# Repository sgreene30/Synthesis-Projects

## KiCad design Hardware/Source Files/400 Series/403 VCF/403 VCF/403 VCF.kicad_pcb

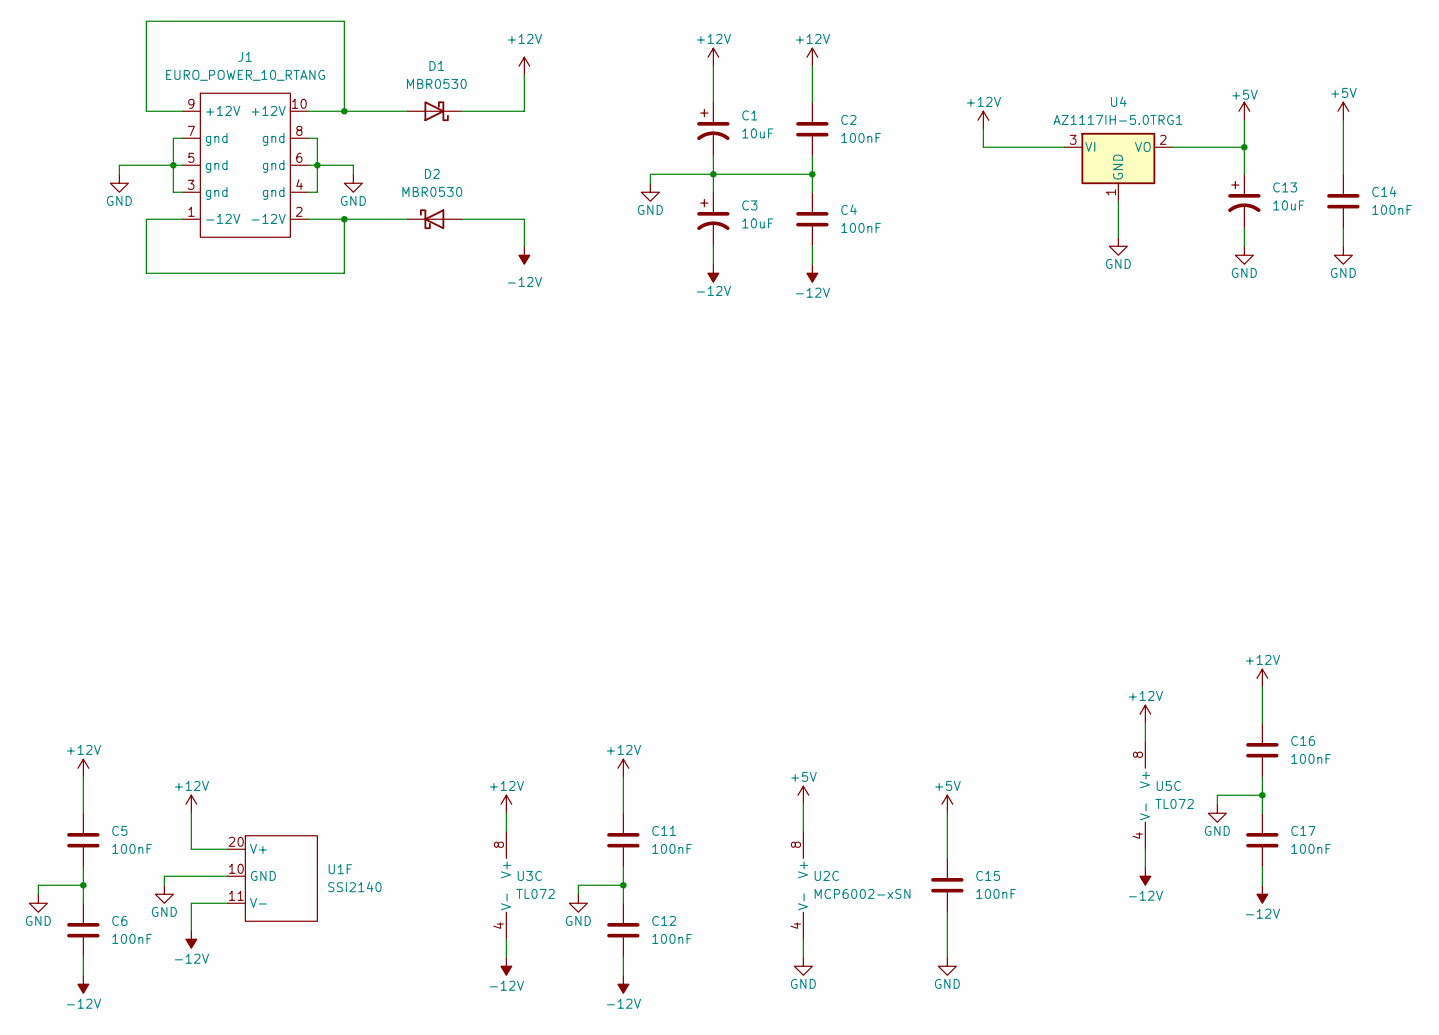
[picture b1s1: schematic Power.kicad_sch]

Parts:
C1, C3, C13: 10uF; C_P_2312_6032; MPN T491C106K025AT; LCSC C116748
C2, C4, C5, C6, C11, C12, C14, C15, C16, C17: 100nF; C_0603_1608Metric; MPN CC0603KRX7R9BB104; LCSC C14663
D1, D2: MBR0530; D_SOD-123; MPN MBR0530T1G; LCSC C82046
J1: EURO_POWER_10_RTANG; MPN 61201021721; LCSC C5117909
U1: SSI2140; SSOP-20_4.4x6.5mm_P0.65mm; MPN SSI2140
U2: MCP6002-xSN; SOIC-8_3.9x4.9mm_P1.27mm; MPN MCP6002T-I/SN; LCSC C7377
U3, U5: TL072; SOIC-8_3.9x4.9mm_P1.27mm; MPN TL072CDR; LCSC C67473
U4: AZ1117IH-5.0TRG1; SOT-223; MPN AZ1117IH-5.0TRG1; LCSC C108496

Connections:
+5V: C13.1, C14.1, C15.1, U2.8 (V+), U4.2 (VO)
+12V: C1.1, C2.1, C5.1, C11.1, C16.1, D1.1 (K), U1.20 (V+), U3.8 (V+), U4.3 (VI), U5.8 (V+); also elsewhere on the board
-12V: C3.2, C4.2, C6.2, C12.2, C17.2, D2.2 (A), U1.11 (V-), U3.4 (V-), U5.4 (V-); also elsewhere on the board
GND: C1.2, C2.2, C3.1, C4.1, C5.2, C6.1, C11.2, C12.1, C13.2, C14.2, C15.2, C16.2, C17.1, J1.3 (gnd), J1.4 (gnd), J1.5 (gnd), J1.6 (gnd), J1.7 (gnd), J1.8 (gnd), U1.10 (GND), U2.4 (V-), U4.1 (GND); also elsewhere on the board
unnamed: D1.2 (A), J1.9 (+12V), J1.10 (+12V)
unnamed: D2.1 (K), J1.1 (-12V), J1.2 (-12V)

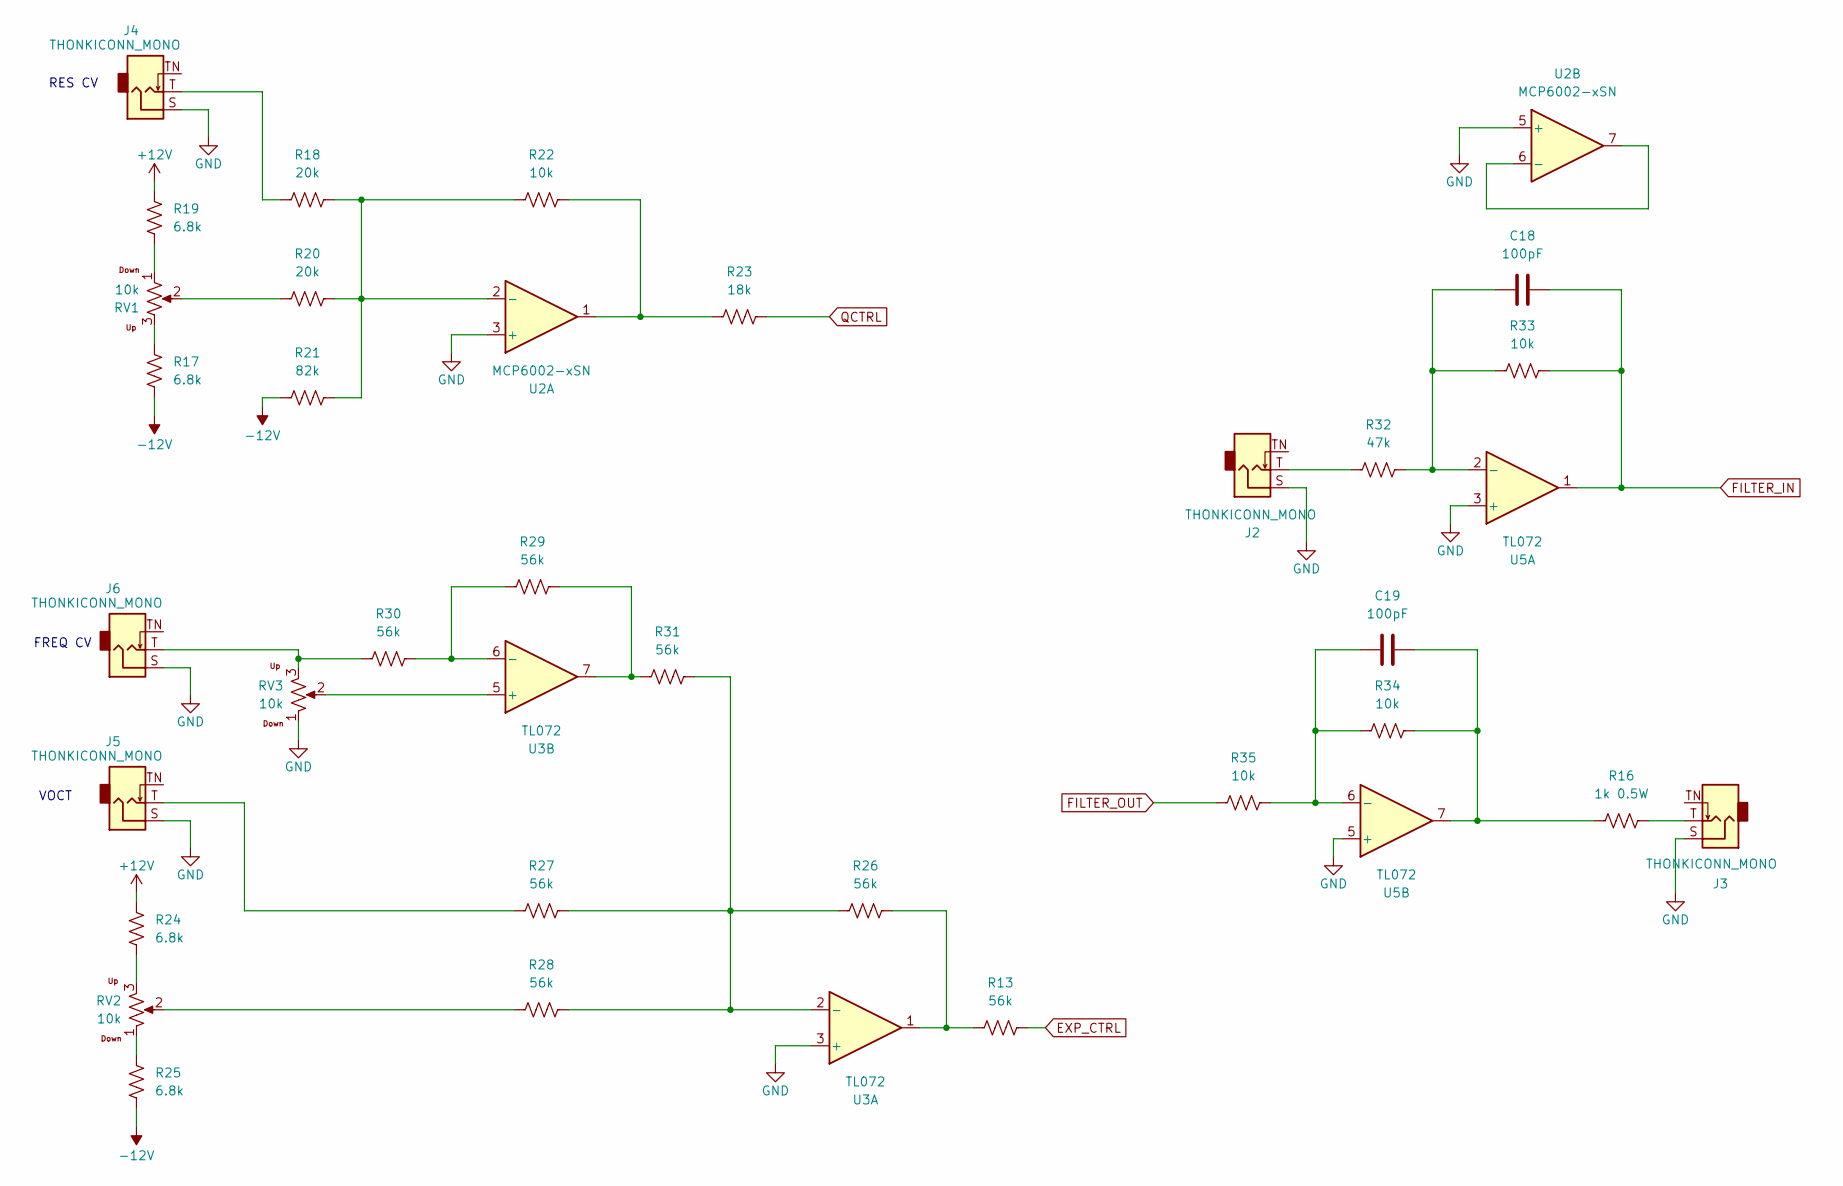
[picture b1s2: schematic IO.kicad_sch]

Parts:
C18, C19: 100pF; C_0603_1608Metric; MPN CC0603JRNPO9BN101; LCSC C14665
J2, J3, J4, J5, J6: THONKICONN_MONO; JACK_THONKICONN_MONO_WQP518MA; MPN WQP518MA
R13, R26, R27, R28, R29, R30, R31: 56k; R_0603_1608Metric; MPN RC0603FR-0756KL; LCSC C114630
R16: 1k 0.5W; R_1210_3225Metric; MPN RC1210FR-071KL; LCSC C83144
R17, R19, R24, R25: 6.8k; R_0603_1608Metric; MPN RC0603FR-076K8L; LCSC C114632
R18, R20: 20k; R_0603_1608Metric; MPN RC0603FR-0720KL; LCSC C105575
R21: 82k; R_0603_1608Metric; MPN RC0603FR-0782KL; LCSC C137678
R22, R33, R34, R35: 10k; R_0603_1608Metric; MPN RC0603FR-0710KL; LCSC C98220
R23: 18k; R_0603_1608Metric; MPN RC0603FR-0718KL; LCSC C114610
R32: 47k; R_0603_1608Metric; MPN RC0603FR-0747KL; LCSC C105579
RV1, RV2, RV3: 10k; ALPHAPOT; MPN RD901F-40-15F-B10K-00D70
U2: MCP6002-xSN; SOIC-8_3.9x4.9mm_P1.27mm; MPN MCP6002T-I/SN; LCSC C7377
U3, U5: TL072; SOIC-8_3.9x4.9mm_P1.27mm; MPN TL072CDR; LCSC C67473

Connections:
+12V: R19.1, R24.1; also elsewhere on the board
-12V: R17.2, R21.1, R25.2; also elsewhere on the board
EXP_CTRL: R13.2; also elsewhere on the board
FILTER_IN: C18.2, R33.2, U5.1; also elsewhere on the board
FILTER_OUT: R35.1; also elsewhere on the board
GND: J2.S, J3.S, J4.S, J5.S, J6.S, RV3.1, U2.3 (+), U2.5 (+), U3.3 (+), U5.3 (+), U5.5 (+); also elsewhere on the board
unnamed: C19.2, R16.1, R34.2, U5.7
unnamed: J2.T, R32.1
unnamed: J3.T, R16.2
unnamed: J4.T, R18.1
unnamed: J5.T, R27.1
unnamed: J6.T, R30.1, RV3.3
unnamed: R13.1, R26.2, U3.1
unnamed: R17.1, RV1.3
unnamed: R19.2, RV1.1
unnamed: R20.1, RV1.2
unnamed: R22.2, R23.1, U2.1
unnamed: R24.2, RV2.3
unnamed: R25.1, RV2.1
unnamed: R28.1, RV2.2
unnamed: R29.2, R31.1, U3.7
unnamed: R18.2, R20.2, R21.2, R22.1, U2.2 (-)
unnamed: U2.6 (-), U2.7
unnamed: R26.1, R27.2, R28.2, R31.2, U3.2 (-)
unnamed: RV3.2, U3.5 (+)
unnamed: R29.1, R30.2, U3.6 (-)
unnamed: C18.1, R32.2, R33.1, U5.2 (-)
unnamed: C19.1, R34.1, R35.2, U5.6 (-)
QCTRL: R23.2; also elsewhere on the board

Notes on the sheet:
RES CV
VOCT
FREQ CV

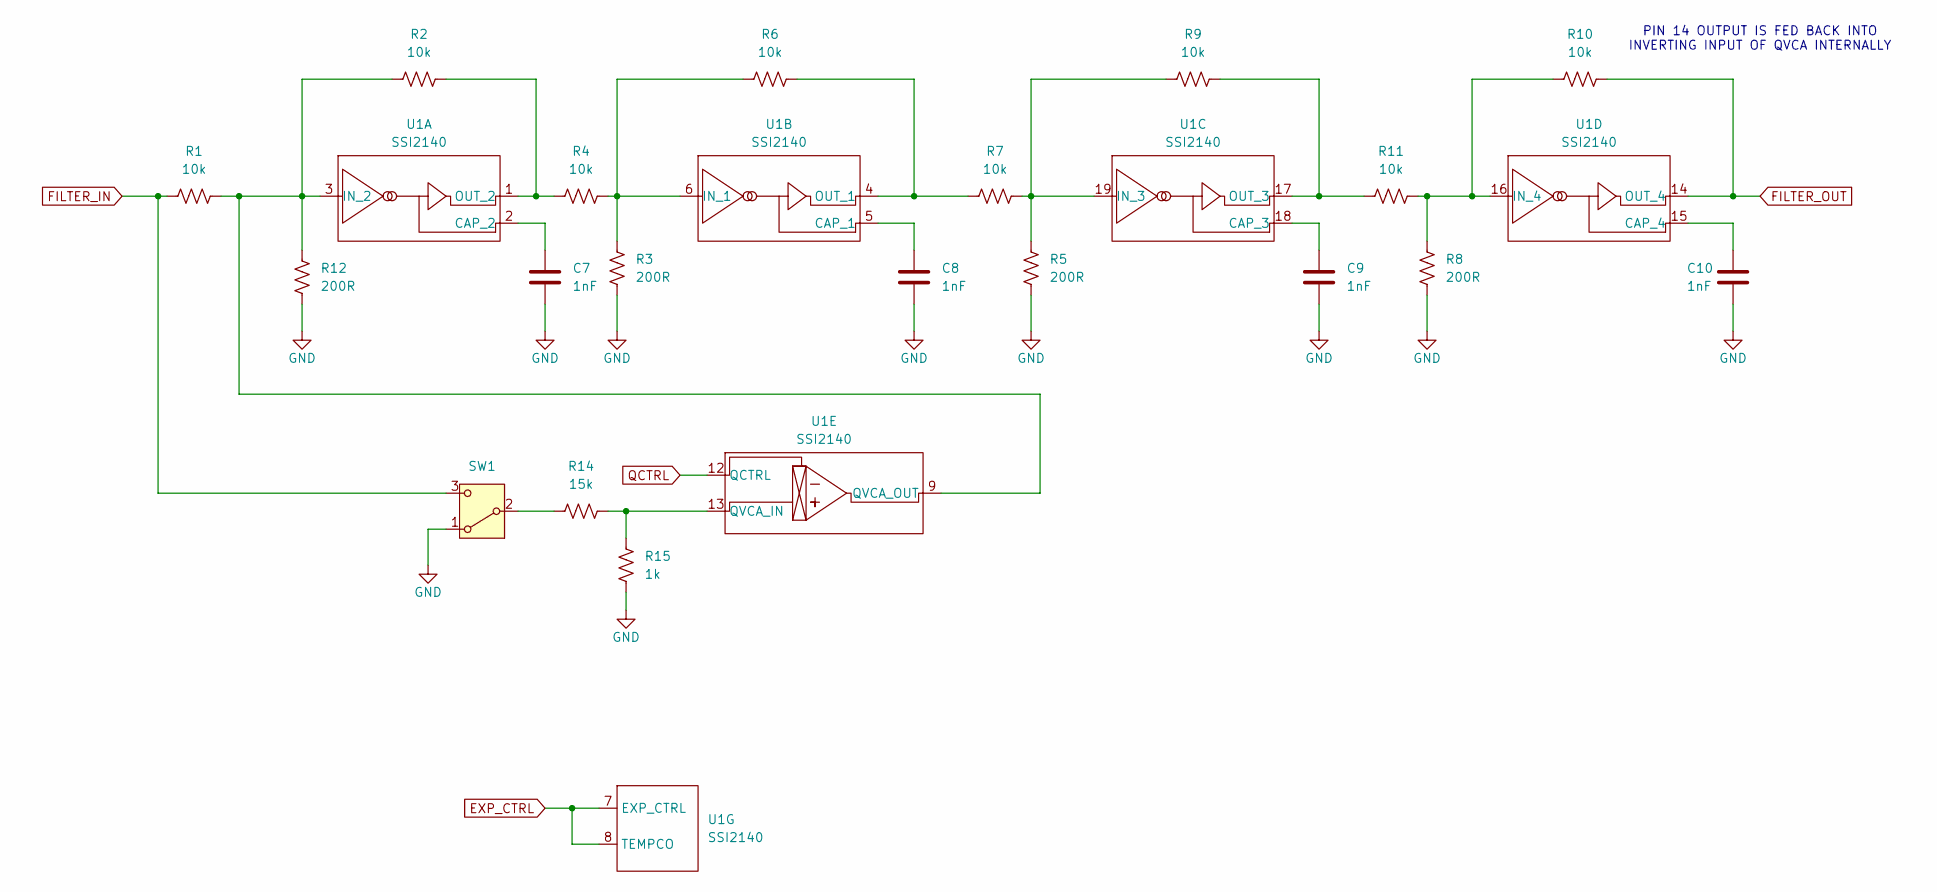
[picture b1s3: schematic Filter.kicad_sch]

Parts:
C7, C8, C9, C10: 1nF; C_0603_1608Metric; MPN CC0603JRNPO8BN102; LCSC C309470
R1, R2, R4, R6, R7, R9, R10, R11: 10k; R_0603_1608Metric; MPN RC0603FR-0710KL; LCSC C98220
R3, R5, R8, R12: 200R; R_0603_1608Metric; MPN RC0603FR-07200RL; LCSC C114664
R14: 15k; R_0603_1608Metric; MPN RC0603FR-0715KL; LCSC C114661
R15: 1k; R_0603_1608Metric; MPN RC0603FR-071KL; LCSC C22548
SW1: SW_SPDT_ON_OFF_ON_SUBMINI; SW_TOGGLE_2MS3T1B3M2QES; MPN 2MS1T1B1M2QES
U1: SSI2140; SSOP-20_4.4x6.5mm_P0.65mm; MPN SSI2140

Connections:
EXP_CTRL: U1.7 (EXP_CTRL), U1.8 (TEMPCO); also elsewhere on the board
FILTER_IN: R1.1, SW1.3 (C); also elsewhere on the board
FILTER_OUT: R10.2, U1.14 (OUT_4); also elsewhere on the board
GND: C7.2, C8.2, C9.2, C10.2, R3.2, R5.2, R8.2, R12.2, R15.2, SW1.1 (A); also elsewhere on the board
unnamed: R14.1, SW1.2 (B)
unnamed: C7.1, U1.2 (CAP_2)
unnamed: R1.2, R2.1, R12.1, U1.3 (IN_2), U1.9 (QVCA_OUT)
unnamed: R2.2, R4.1, U1.1 (OUT_2)
unnamed: C8.1, U1.5 (CAP_1)
unnamed: R3.1, R4.2, R6.1, U1.6 (IN_1)
unnamed: R6.2, R7.1, U1.4 (OUT_1)
unnamed: C9.1, U1.18 (CAP_3)
unnamed: R5.1, R7.2, R9.1, U1.19 (IN_3)
unnamed: R9.2, R11.1, U1.17 (OUT_3)
unnamed: C10.1, U1.15 (CAP_4)
unnamed: R8.1, R10.1, R11.2, U1.16 (IN_4)
unnamed: R14.2, R15.1, U1.13 (QVCA_IN)
QCTRL: U1.12 (QCTRL); also elsewhere on the board

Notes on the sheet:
PIN 14 OUTPUT IS FED BACK INTO INVERTING INPUT OF QVCA INTERNALLY

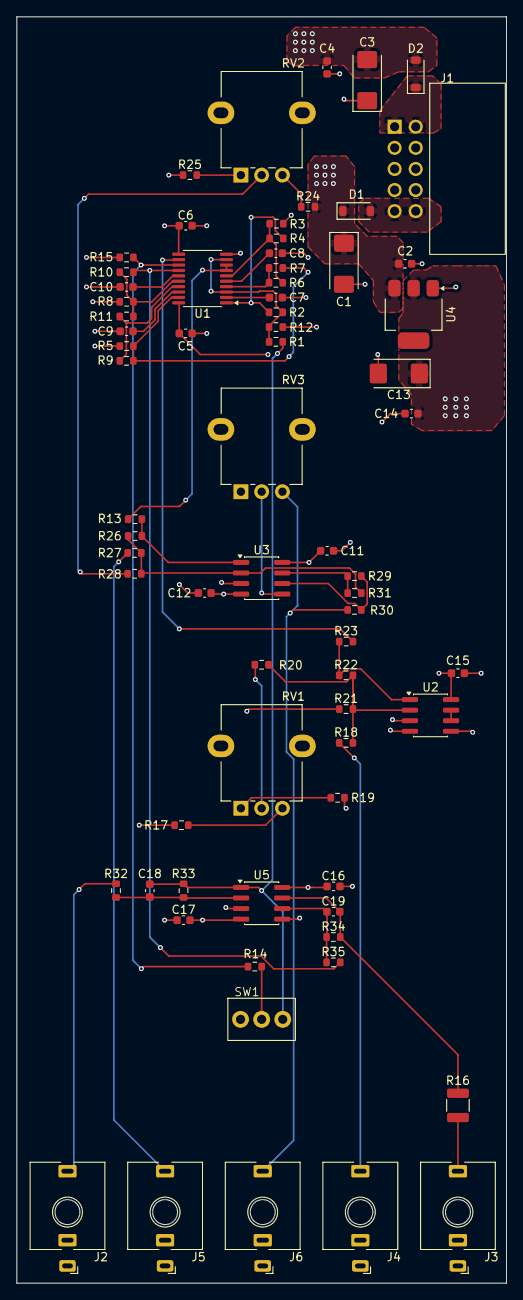
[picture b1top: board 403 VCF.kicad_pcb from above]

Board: 4 copper layers, 58.9 x 152.4 mm, 71 parts (0 on the bottom side), 45 nets.

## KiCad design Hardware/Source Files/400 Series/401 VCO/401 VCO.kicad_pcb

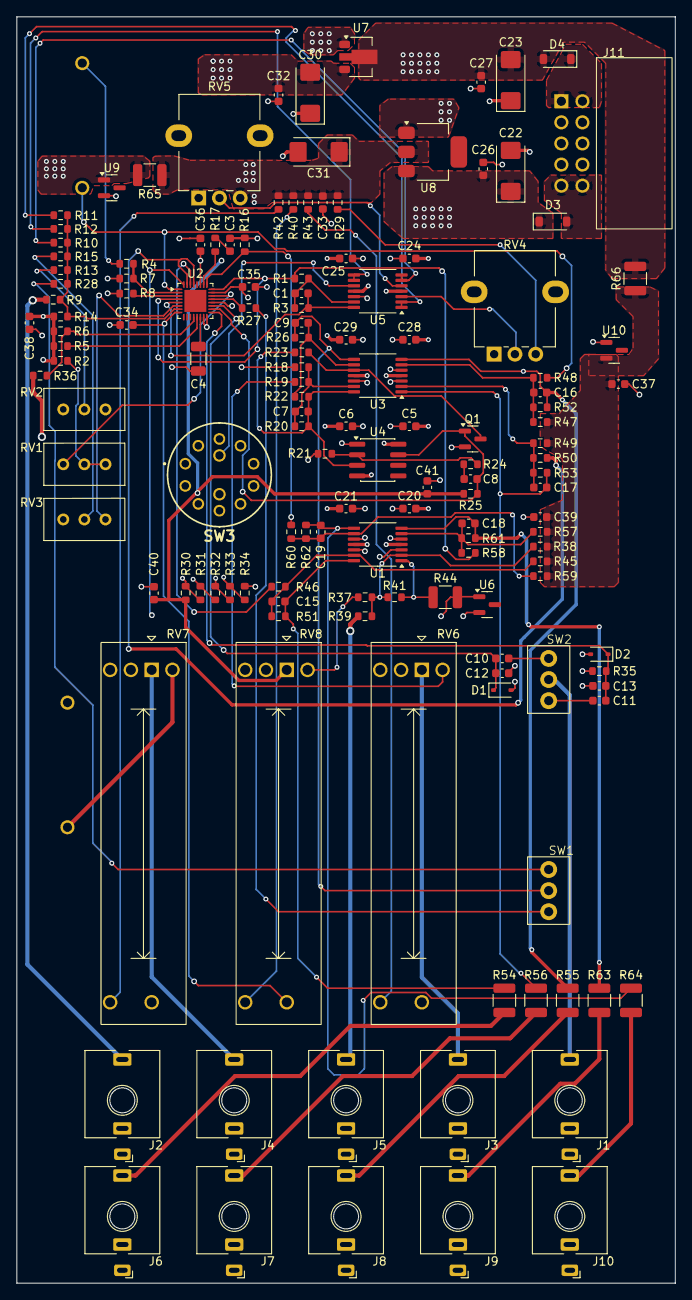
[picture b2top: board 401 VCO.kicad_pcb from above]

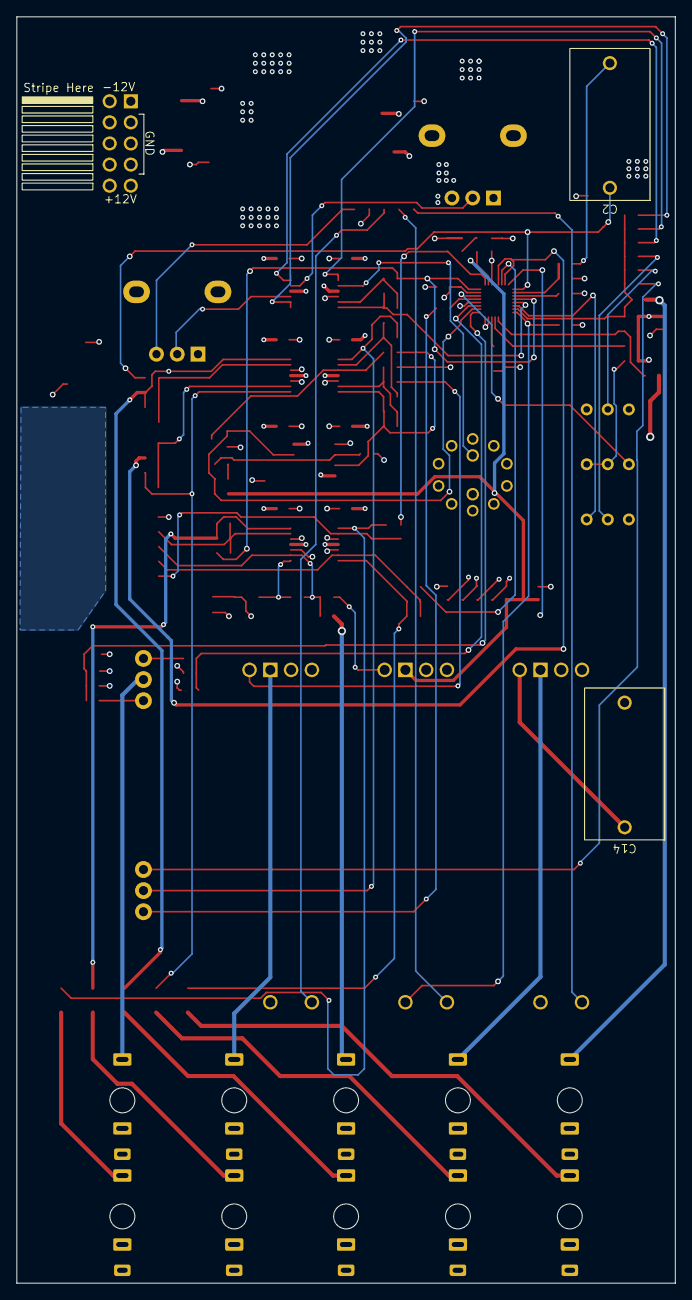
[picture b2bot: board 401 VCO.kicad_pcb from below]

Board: 4 copper layers, 79.2 x 152.4 mm, 144 parts (2 on the bottom side), 86 nets.

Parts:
C1, C7, C8, C9, C15, C16, C17, C18, C19: 100pF; C_0603_1608Metric
C2, C14: 10uF; CAP_B32522C0106K189
C3, C10, C11, C12, C13: 10nF; C_0603_1608Metric
C4: 3.9nF; C_1206_3216Metric
C5, C6, C20, C21, C24, C25, C26, C27, C28, C29, C32, C33, C34, C35, C36, C37, C38, C39, C40, C41: 100nF; C_0603_1608Metric
C22, C23, C30, C31: 10uF; C_P_2312_6032
D1, D2: 1N4148; D_SOD-323
D3, D4: MBR0530; D_SOD-123
J1, J2, J3, J4, J5, J6, J7, J8, J9, J10: THONKICONN_MONO; JACK_THONKICONN_MONO_WQP518MA
J11: EURO_POWER_10_RTANG
Q1: 2N7002; SOT-23
R1, R3, R13, R16, R25, R30, R31, R32, R33, R34, R35: 10k; R_0603_1608Metric
R2, R18, R19, R20, R22, R23, R26: 22k; R_0603_1608Metric
R4: 3.9k; R_0603_1608Metric
R5, R6, R14, R24, R58, R60: 100k; R_0603_1608Metric
R7, R8: 4.7k; R_0603_1608Metric
R9, R10, R11, R12, R36: 47k; R_0603_1608Metric
R15: 270k; R_0603_1608Metric
R17: 270R; R_0603_1608Metric
R21: 100R; R_0603_1608Metric
R27, R28: 470k; R_0603_1608Metric
R29: 15k; R_0603_1608Metric
R37, R38, R39, R45, R47, R49, R51, R52, R53, R57, R59: 120k; R_0603_1608Metric
R40, R42, R43: 330R; R_0603_1608Metric
R41, R46, R48, R50: 30k; R_0603_1608Metric
R44, R54, R55, R56, R63, R64, R65, R66: 1k 0.5W; R_1210_3225Metric
R61, R62: 200k; R_0603_1608Metric
RV1, RV2, RV3: 5K; TRIMPOT_PV36
RV4, RV5: 10k; ALPHAPOT
RV6, RV7, RV8: 10k; Potentiometer_Slide_PTL30
SW1, SW2: SW_SPDT_ON_OFF_ON_SUBMINI; SW_TOGGLE_2MS3T1B3M2QES
SW3: SWITCH; 56DP36012AJN
U1, U3, U5: TL074CPWR; TSSOP-14_4.4x5mm_P0.65mm
U2: SSI2130; QFN-32-1EP_4x4mm_P0.4mm_EP2.65x2.65mm
U4: LM311; SOIC-8_3.9x4.9mm_P1.27mm
U6, U9: VREF_2.5V_0.2%; SOT-23
U7: L79L05ABUTR; SOT-89-3
U8: AZ1117IH-5.0TRG1; SOT-223
U10: LM4040CIM3-5.0; SOT-23

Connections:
+2V5: C35.1, C38.1, R2.1, R5.1, R6.1, R14.1, R18.1, R65.2, RV2.1, U2.23 (VREF), U9.1 (K)
+5V: C31.1, C33.1, C36.1, C40.1, C41.1, R25.1, R29.1, R30.1, R40.1, R42.1, R43.1, R65.1, RV5.3, RV8.1, U2.27 (V+), U8.2 (VO)
+12V: C5.1, C20.1, C22.1, C24.1, C26.1, C28.1, D3.1 (K), U1.4 (V+), U3.4 (V+), U4.8 (V+), U5.4 (V+), U8.3 (VI)
-5V: C37.2, C39.2, R38.1, R45.1, R47.1, R49.1, R57.1, R59.1, R66.1, U10.2 (A)
-5VA: C30.2, C32.1, C34.1, RV5.1, RV8.3, U2.8 (V-), U7.3 (VO)
-12V: C6.2, C21.2, C23.2, C25.2, C27.2, C29.2, D4.2 (A), R66.2, U1.11 (V-), U3.11 (V-), U4.4 (V-), U5.11 (V-), U7.2 (VI)
/IO/AM: J4.T, RV7.1
/IO/AM_N1: C14.1, RV7.2
/IO/AM_N2: C14.2, R36.1
/IO/PWM: J5.T, R39.1
/IO/SYNC: J1.T, SW2.2 (B)
/IO/TZFM: J3.T, RV6.1
/SSI2130/AUX_2_IN: C1.2, R3.2, U2.5 (AUX_2_IN), U5.14
/SSI2130/AUX_2_MIX: R5.2, U2.13 (AUX_2_MIX)
/SSI2130/BW_COMP: R17.1, U2.26 (BW_COMP)
/SSI2130/SINE_IN+: R4.2, R7.1, U2.2 (SINE_IN+)
/SSI2130/SINE_IN-: R8.1, U2.3 (SINE_IN-)
/SSI2130/TCAP: C4.1, U2.14 (TCAP)
AM: R16.2, R60.1, U2.25 (MIX_OUT)
AM_IN: R6.2, R36.2, U2.12 (AUX_1_MIX)
AM_OUT: J10.T, R64.2
COARSE: R10.1, U5.6 (-), U5.7
EXPO_FREQ: R9.2, R10.2, R11.2, R12.2, R13.2, R14.2, R15.2, R28.2, U2.7 (EXPO_FREQ)
EXPO_SCALE: RV1.3, U2.22 (EXPO_SCALE)
FINE: R11.1, U5.1, U5.2 (-)
GND: C3.2, C4.2, C5.2, C6.1, C12.2, C13.2, C20.2, C21.1, C22.2, C23.1, C24.2, C25.1, C26.2, C27.1, C28.2, C29.1, C30.1, C31.2, C32.2, C33.2, C34.2, C35.2, C36.2, C37.1, C38.2, C39.1, C40.2, C41.2, D1.2 (A), D2.2 (A), J1.S, J2.S, J3.S, J4.S, J5.S, J6.S, J7.S, J8.S, J9.S, J10.S, J11.3 (gnd), J11.4 (gnd), J11.5 (gnd), J11.6 (gnd), J11.7 (gnd), J11.8 (gnd), Q1.2 (S), R7.2, R8.2, R16.1, R21.2, R34.2, R35.2, RV2.3, RV3.3, RV4.1, RV6.3, RV6.E, RV7.3, RV7.E, RV8.E, SW3.5, U1.3 (+), U1.5 (+), U1.10 (+), U1.12 (+), U2.15 (DGND), U2.16 (AGND), U2.20 (HFT_BASE), U3.3 (+), U3.5 (+), U3.12 (+), U4.1 (GND), U5.12 (+), U6.2 (A), U7.1 (GND), U8.1 (GND), U9.2 (A), U10.1 (K)
HARD_SYNC: C11.2, C13.1, D2.1 (K), R35.1, U2.17 (HARD_SYNC)
HF_TRACK: RV3.1, U2.6 (HF_TRACK)
LIN_FREQ: R27.2, U2.21 (LIN_FREQ)
unnamed: C2.2, R4.1
unnamed: C3.1, R17.2
unnamed: C8.1, R24.2
unnamed: C15.2, R51.2, R54.1, U1.14
unnamed: C16.2, R52.2, R55.1, U3.7
unnamed: C17.2, R53.2, R56.1, U3.1
unnamed: C18.2, R61.2, R63.1, U1.7
unnamed: C19.2, R62.2, R64.1, U1.8
unnamed: D3.2 (A), J11.9 (+12V), J11.10 (+12V)
unnamed: D4.1 (K), J11.1 (-12V), J11.2 (-12V)
unnamed: Q1.3 (D), R23.2, U3.10 (+)
unnamed: R2.2, RV1.1, RV1.2
unnamed: R13.1, RV2.2
unnamed: R15.1, RV3.2
unnamed: R29.2, RV4.3
unnamed: R30.2, R31.1, SW3.1
unnamed: R31.2, R32.1, SW3.2
unnamed: R32.2, R33.1, SW3.3
unnamed: R33.2, R34.1, SW3.4
unnamed: R37.1, RV8.2
unnamed: R40.2, RV8.B
unnamed: R41.2, R44.1, U1.1
unnamed: R42.2, RV7.B
unnamed: R43.2, RV6.B
unnamed: R27.1, SW1.1 (A)
unnamed: C9.2, R26.2, SW1.2 (B), U3.8
unnamed: R28.1, SW1.3 (C)
unnamed: C11.1, SW2.1 (A)
unnamed: C10.1, SW2.3 (C)
unnamed: R37.2, R38.2, R39.2, R41.1, U1.2 (-)
unnamed: C18.1, R57.2, R58.2, R61.1, U1.6 (-)
unnamed: C19.1, R59.2, R60.2, R62.1, U1.9 (-)
unnamed: C15.1, R45.2, R46.2, R51.1, U1.13 (-)
unnamed: C17.1, R49.2, R50.2, R53.1, U3.2 (-)
unnamed: C16.1, R47.2, R48.2, R52.1, U3.6 (-)
unnamed: C9.1, R22.2, R26.1, U3.9 (-)
unnamed: C7.1, R18.2, R19.2, R20.1, U3.13 (-)
unnamed: R21.1, R24.1, U4.2 (+)
unnamed: C7.2, R20.2, R22.1, R23.1, U3.14, U4.3 (-)
unnamed: RV4.2, U5.3 (+)
unnamed: RV5.2, U5.5 (+)
unnamed: SW3.11, U5.10 (+)
unnamed: C1.1, R1.2, R3.1, U5.13 (-)
OCTAVE: R12.1, U5.8, U5.9 (-)
PULSE: R46.1, U2.30 (PULSE_OUT)
PULSE_OUT: J6.T, R54.2
PWM+: R44.2, U2.32 (PWM+), U6.1 (K)
SAW: R50.1, U2.29 (SAW_OUT), U2.31 (PWM-)
SAW_OUT: J7.T, R56.2
SINE: R1.1, R58.1, U2.4 (AUX_1_IN), U2.24 (SINE_OUT)
SINE_OUT: J9.T, R63.2
SOFT_SYNC: C10.2, C12.1, D1.1 (K), U2.19 (SOFT_SYNC)
TIME_REVERSE: C8.2, Q1.1 (G), R25.2, U2.18 (TIME_REVERSE), U4.7
TRIANGLE: C2.1, R48.1, U2.1 (TRI_OUT)
TRIANGLE_OUT: J8.T, R55.2
TZFM_IN: R19.1, RV6.2
VOCT: J2.T, R9.1

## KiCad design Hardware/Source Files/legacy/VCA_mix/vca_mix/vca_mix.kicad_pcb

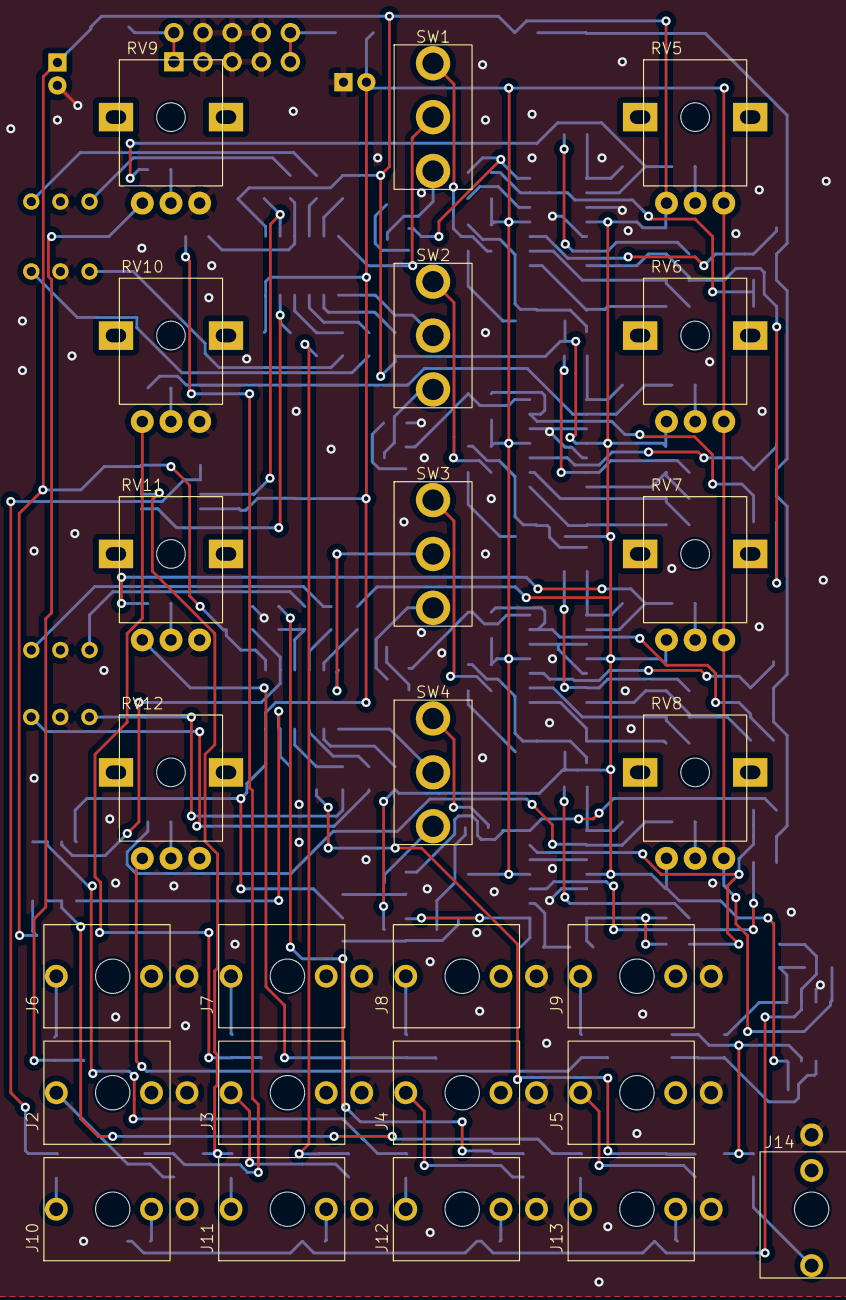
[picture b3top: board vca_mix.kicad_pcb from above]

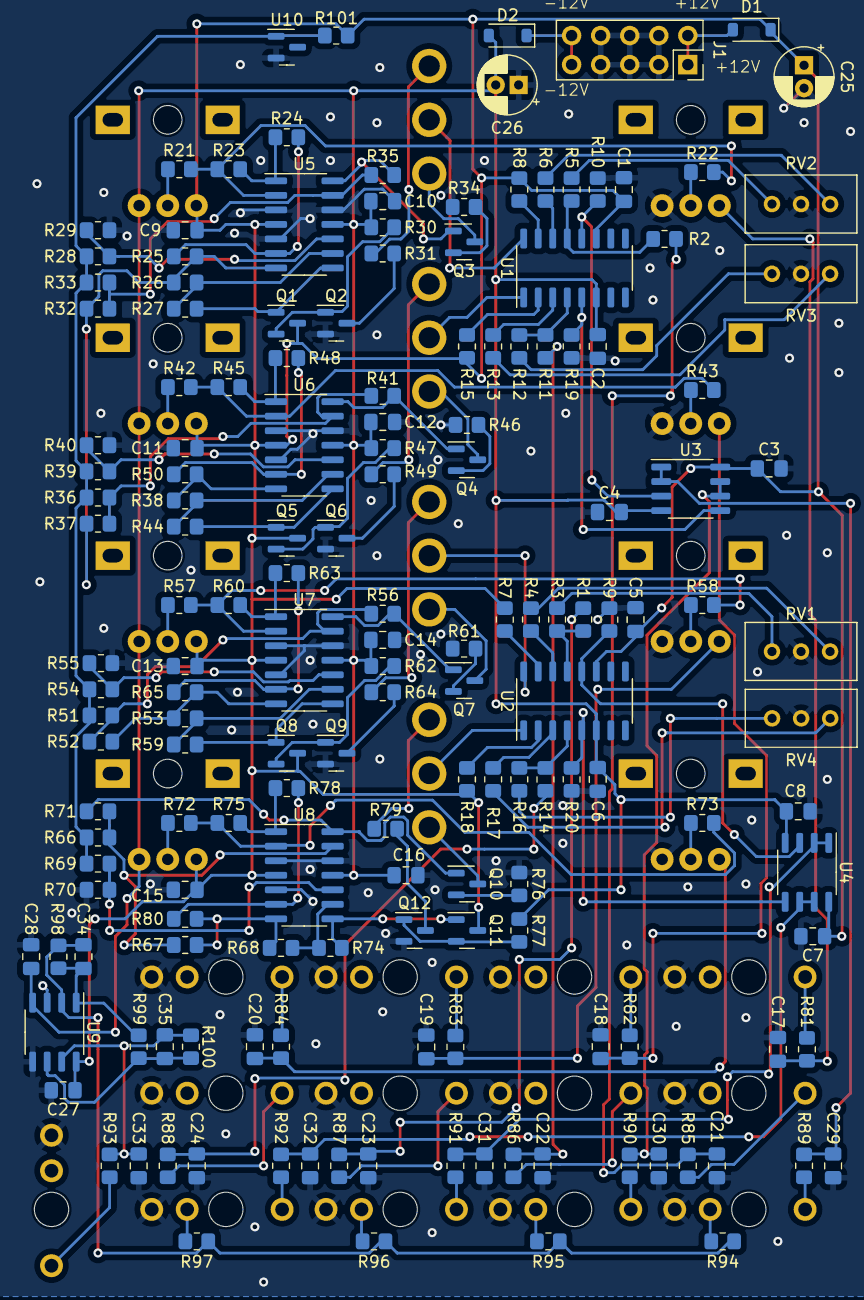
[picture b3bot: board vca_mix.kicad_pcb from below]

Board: 2 copper layers, 190 parts (165 on the bottom side), 131 nets.

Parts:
C1, C2, C3, C4, C5, C6, C7, C8, C9, C10, C11, C12, C13, C14, C15, C16, C27, C28: 100n; C_0805_2012Metric_Pad1.18x1.45mm_HandSolder
C17, C18, C19, C20, C21, C22, C23, C24, C29, C30, C31, C32, C33: DNP; C_0805_2012Metric_Pad1.18x1.45mm_HandSolder
C25, C26: 10u; CP_Radial_D5.0mm_P2.00mm
C34, C35: 100p; C_0805_2012Metric_Pad1.18x1.45mm_HandSolder
D1: MBR0530-TP; D_SOD-123
D2: D_Schottky; D_SOD-123
J1: power; PinSocket_2x05_P2.54mm_Vertical
J2, J3, J4, J5, J6, J7, J8, J9, J10, J11, J12, J13, J14: Thonkiconn; thonkiconn
Q1, Q5, Q8, Q11: MMBT3904; SOT-23
Q2, Q3, Q4, Q6, Q7, Q9, Q10, Q12: MMBT3906; SOT-23
R1, R2, R11, R14, R31, R32, R34, R37, R46, R49, R52, R61, R64, R67, R76, R79, R98, R99: 20k; R_0805_2012Metric_Pad1.20x1.40mm_HandSolder
R3, R4, R5, R6, R12, R13, R16, R17: 430R; R_0805_2012Metric_Pad1.20x1.40mm_HandSolder
R7, R8, R15, R18, R24, R25, R28, R35, R39, R41, R48, R50, R54, R56, R63, R65, R69, R71, R78, R80, R94, R95, R96, R97, R100: 10k; R_0805_2012Metric_Pad1.20x1.40mm_HandSolder
R9, R10, R19, R20: 47k; R_0805_2012Metric_Pad1.20x1.40mm_HandSolder
R21, R23, R26, R38, R42, R45, R53, R57, R60, R68, R72, R75: 200k; R_0805_2012Metric_Pad1.20x1.40mm_HandSolder
R22, R43, R58, R73: 100k; R_0805_2012Metric_Pad1.20x1.40mm_HandSolder
R27, R44, R59, R74: 3k; R_0805_2012Metric_Pad1.20x1.40mm_HandSolder
R29, R40, R55, R70: 330; R_0805_2012Metric_Pad1.20x1.40mm_HandSolder
R30, R47, R62, R77: 120k; R_0805_2012Metric_Pad1.20x1.40mm_HandSolder
R33, R36, R51, R66: 6k2; R_0805_2012Metric_Pad1.20x1.40mm_HandSolder
R81, R82, R83, R84, R85, R86, R87, R88: 0R; R_0805_2012Metric_Pad1.20x1.40mm_HandSolder
R89, R90, R91, R92, R93: 100R; R_0805_2012Metric_Pad1.20x1.40mm_HandSolder
R101: 470; R_0805_2012Metric_Pad1.20x1.40mm_HandSolder
RV1, RV2, RV3, RV4: 100R; Potentiometer_Bourns_3296W_Vertical
RV5, RV6, RV7, RV8, RV9, RV10, RV11, RV12: 10k; alpha_pot
SW1, SW2, SW3, SW4: SW_SPDT; Mini_sw
U1, U2: LM13700; SO-16_3.9x9.9mm_P1.27mm
U3, U4, U9: TL072; SO-8_3.9x4.9mm_P1.27mm
U5, U6, U7, U8: TL074; SO-14_3.9x8.65mm_P1.27mm
U10: LM4040DBZ-3; SOT-23

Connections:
+3V0: R28.1, R33.1, R36.1, R39.1, R51.1, R54.1, R66.1, R69.1, R101.2, U10.1 (K)
+12V: C1.1, C3.1, C5.1, C7.1, C9.1, C11.1, C13.1, C15.1, C25.1, C27.1, D1.1 (K), Q1.3 (C), Q5.3 (C), Q8.3 (C), Q11.3 (C), R7.2, R8.2, R15.2, R18.2, R101.1, RV5.1, RV6.1, RV7.1, RV8.1, U1.11 (V+), U2.11 (V+), U3.8 (V+), U4.8 (V+), U5.4 (V+), U6.4 (V+), U7.4 (V+), U8.4 (V+), U9.8 (V+)
-12V: C2.2, C4.2, C6.2, C8.2, C10.2, C12.2, C14.2, C16.2, C26.2, C28.2, D2.2 (A), R30.1, R47.1, R62.1, R77.1, RV5.3, RV6.3, RV7.3, RV8.3, U1.6 (V-), U2.6 (V-), U3.4 (V-), U4.4 (V-), U5.11 (V-), U6.11 (V-), U7.11 (V-), U8.11 (V-), U9.4 (V-)
/IO/MIX_OUT: C33.1, C35.2, R93.2, R100.2, U9.7
/IO/VCA_1_MIX: J10.TN, R94.1
/IO/VCA_2_MIX: J11.TN, R95.1
/IO/VCA_3_MIX: J12.TN, R96.1
/IO/VCA_4_MIX: J13.TN, R97.1
/VC/EXP_IABC_1: R31.1, SW1.3 (C)
/VC/EXP_IABC_2: R49.1, SW2.3 (C)
/VC/LIN_IABC_1: Q3.3 (C), SW1.1 (A)
/VC/LIN_IABC_2: Q4.3 (C), SW2.1 (A)
/VC/VC_1: R25.2, R26.1, R32.1, R37.1, U5.7
/VC/VC_2: R38.1, R50.2, U6.7
/VC_2/EXP_IABC_3: R64.1, SW3.3 (C)
/VC_2/EXP_IABC_4: R79.1, SW4.3 (C)
/VC_2/LIN_IABC_3: Q7.3 (C), SW3.1 (A)
/VC_2/LIN_IABC_4: Q10.3 (C), SW4.1 (A)
/VC_2/VC_3: R52.1, R53.1, R65.2, U7.7
/VC_2/VC_4: R67.1, R68.1, R80.2, U8.7
GND: C1.2, C2.1, C3.2, C4.1, C5.2, C6.1, C7.2, C8.1, C9.2, C10.1, C11.2, C12.1, C13.2, C14.1, C15.2, C16.1, C17.2, C18.2, C19.2, C20.2, C21.2, C22.2, C23.2, C24.2, C25.2, C26.1, C27.2, C28.1, C29.2, C30.2, C31.2, C32.2, C33.2, J1.3, J1.4, J1.5, J1.6, J1.7, J1.8, J2.S, J3.S, J4.S, J5.S, J6.S, J7.S, J8.S, J9.S, J10.S, J11.S, J12.S, J13.S, J14.S, Q2.2 (E), Q6.2 (E), Q9.2 (E), Q12.2 (E), R9.1, R10.1, R19.1, R20.1, R29.2, R34.1, R40.2, R46.1, R55.2, R61.1, R70.2, R76.1, RV1.2, RV2.2, RV3.2, RV4.2, RV9.3, RV10.3, RV11.3, RV12.3, U5.3 (+), U5.5 (+), U5.12 (+), U6.3 (+), U6.5 (+), U6.12 (+), U7.3 (+), U7.5 (+), U7.12 (+), U8.3 (+), U8.5 (+), U8.12 (+), U9.3 (+), U9.5 (+), U10.2 (A)
unnamed: C17.1, R81.2, RV9.1
unnamed: C18.1, R82.2, RV10.1
unnamed: C19.1, R83.2, RV11.1
unnamed: C20.1, R84.2, RV12.1
unnamed: C34.2, R98.2, R99.1, U9.1
unnamed: D1.2 (A), J1.1, J1.2
unnamed: D2.1 (K), J1.9, J1.10
unnamed: J2.T, R85.1
unnamed: J3.T, R86.1
unnamed: J4.T, R87.1
unnamed: J5.T, R88.1
unnamed: J6.T, R81.1
unnamed: J7.T, R82.1
unnamed: J8.T, R83.1
unnamed: J9.T, R84.1
unnamed: J10.T, R89.1
unnamed: J11.T, R90.1
unnamed: J12.T, R91.1
unnamed: J13.T, R92.1
unnamed: J14.T, R93.1
unnamed: Q1.1 (B), R27.2, U5.8
unnamed: Q1.2 (E), Q2.1 (B), R30.2
unnamed: Q2.3 (C), R31.2
unnamed: Q3.1 (B), R35.2, U5.14
unnamed: Q3.2 (E), R34.2
unnamed: Q4.1 (B), R41.2, U6.14
unnamed: Q4.2 (E), R46.2
unnamed: Q5.1 (B), R44.2, U6.8
unnamed: Q5.2 (E), Q6.1 (B), R47.2
unnamed: Q6.3 (C), R49.2
unnamed: Q7.1 (B), R56.2, U7.14
unnamed: Q7.2 (E), R61.2
unnamed: Q8.1 (B), R59.2, U7.8
unnamed: Q8.2 (E), Q9.1 (B), R62.2
unnamed: Q9.3 (C), R64.2
unnamed: Q10.1 (B), R71.2, U8.14
unnamed: Q10.2 (E), R76.2
unnamed: Q11.1 (B), R74.2, U8.8
unnamed: Q11.2 (E), Q12.1 (B), R77.2
unnamed: Q12.3 (C), R79.2
unnamed: R3.1, RV1.1
unnamed: R4.2, RV1.3
unnamed: R5.1, RV2.1
unnamed: R6.2, RV2.3
unnamed: R12.1, RV3.1
unnamed: R13.2, RV3.3
unnamed: R16.1, RV4.1
unnamed: R17.2, RV4.3
unnamed: R21.1, RV5.2
unnamed: R23.2, R24.1, U5.1
unnamed: R42.1, RV6.2
unnamed: R45.2, R48.1, U6.1
unnamed: R57.1, RV7.2
unnamed: R60.2, R63.1, U7.1
unnamed: R72.1, RV8.2
unnamed: R75.2, R78.1, U8.1
unnamed: R6.1, U1.14 (+)
unnamed: R2.2, R5.2, U1.13 (-)
unnamed: R8.1, U1.15 (DIODE_BIAS)
unnamed: R13.1, U1.3 (+)
unnamed: R11.2, R12.2, U1.4 (-)
unnamed: R15.1, U1.2 (DIODE_BIAS)
unnamed: R4.1, U2.14 (+)
unnamed: R1.2, R3.2, U2.13 (-)
unnamed: R7.1, U2.15 (DIODE_BIAS)
unnamed: R17.1, U2.3 (+)
unnamed: R14.2, R16.2, U2.4 (-)
unnamed: R18.1, U2.2 (DIODE_BIAS)
unnamed: R10.2, U1.12, U3.3 (+)
unnamed: R19.2, U1.5, U3.5 (+)
unnamed: R9.2, U2.12, U4.3 (+)
unnamed: R20.2, U2.5, U4.5 (+)
unnamed: R21.2, R22.2, R23.1, U5.2 (-)
unnamed: R24.2, R25.1, U5.6 (-)
unnamed: R28.2, R29.1, U5.10 (+)
unnamed: R26.2, R27.1, U5.9 (-)
unnamed: R32.2, R33.2, R35.1, U5.13 (-)
unnamed: R42.2, R43.2, R45.1, U6.2 (-)
unnamed: R48.2, R50.1, U6.6 (-)
unnamed: R39.2, R40.1, U6.10 (+)
unnamed: R38.2, R44.1, U6.9 (-)
unnamed: R36.2, R37.2, R41.1, U6.13 (-)
unnamed: R57.2, R58.2, R60.1, U7.2 (-)
unnamed: R63.2, R65.1, U7.6 (-)
unnamed: R54.2, R55.1, U7.10 (+)
unnamed: R53.2, R59.1, U7.9 (-)
unnamed: R51.2, R52.2, R56.1, U7.13 (-)
unnamed: R72.2, R73.2, R75.1, U8.2 (-)
unnamed: R78.2, R80.1, U8.6 (-)
unnamed: R69.2, R70.1, U8.10 (+)
unnamed: R68.2, R74.1, U8.9 (-)
unnamed: R66.2, R67.2, R71.1, U8.13 (-)
unnamed: C34.1, R94.2, R95.2, R96.2, R97.2, R98.1, U9.2 (-)
unnamed: C35.1, R99.2, R100.1, U9.6 (-)
VCA_1_CV: R22.1, RV9.2
VCA_1_IABC: SW1.2 (B), U1.16
VCA_1_IN: C21.1, R2.1, R85.2
VCA_1_OUT: C29.1, R89.2, U3.1, U3.2 (-)
VCA_2_CV: R43.1, RV10.2
VCA_2_IABC: SW2.2 (B), U1.1
VCA_2_IN: C22.1, R11.1, R86.2
VCA_2_OUT: C30.1, R90.2, U3.6 (-), U3.7
VCA_3_CV: R58.1, RV11.2
VCA_3_IABC: SW3.2 (B), U2.16
VCA_3_IN: C23.1, R1.1, R87.2
VCA_3_OUT: C31.1, R91.2, U4.1, U4.2 (-)
VCA_4_CV: R73.1, RV12.2
VCA_4_IABC: SW4.2 (B), U2.1
VCA_4_IN: C24.1, R14.1, R88.2
VCA_4_OUT: C32.1, R92.2, U4.6 (-), U4.7
